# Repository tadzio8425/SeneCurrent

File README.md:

<div>
  <h1>  SeneCurrent  </h1>
</div>

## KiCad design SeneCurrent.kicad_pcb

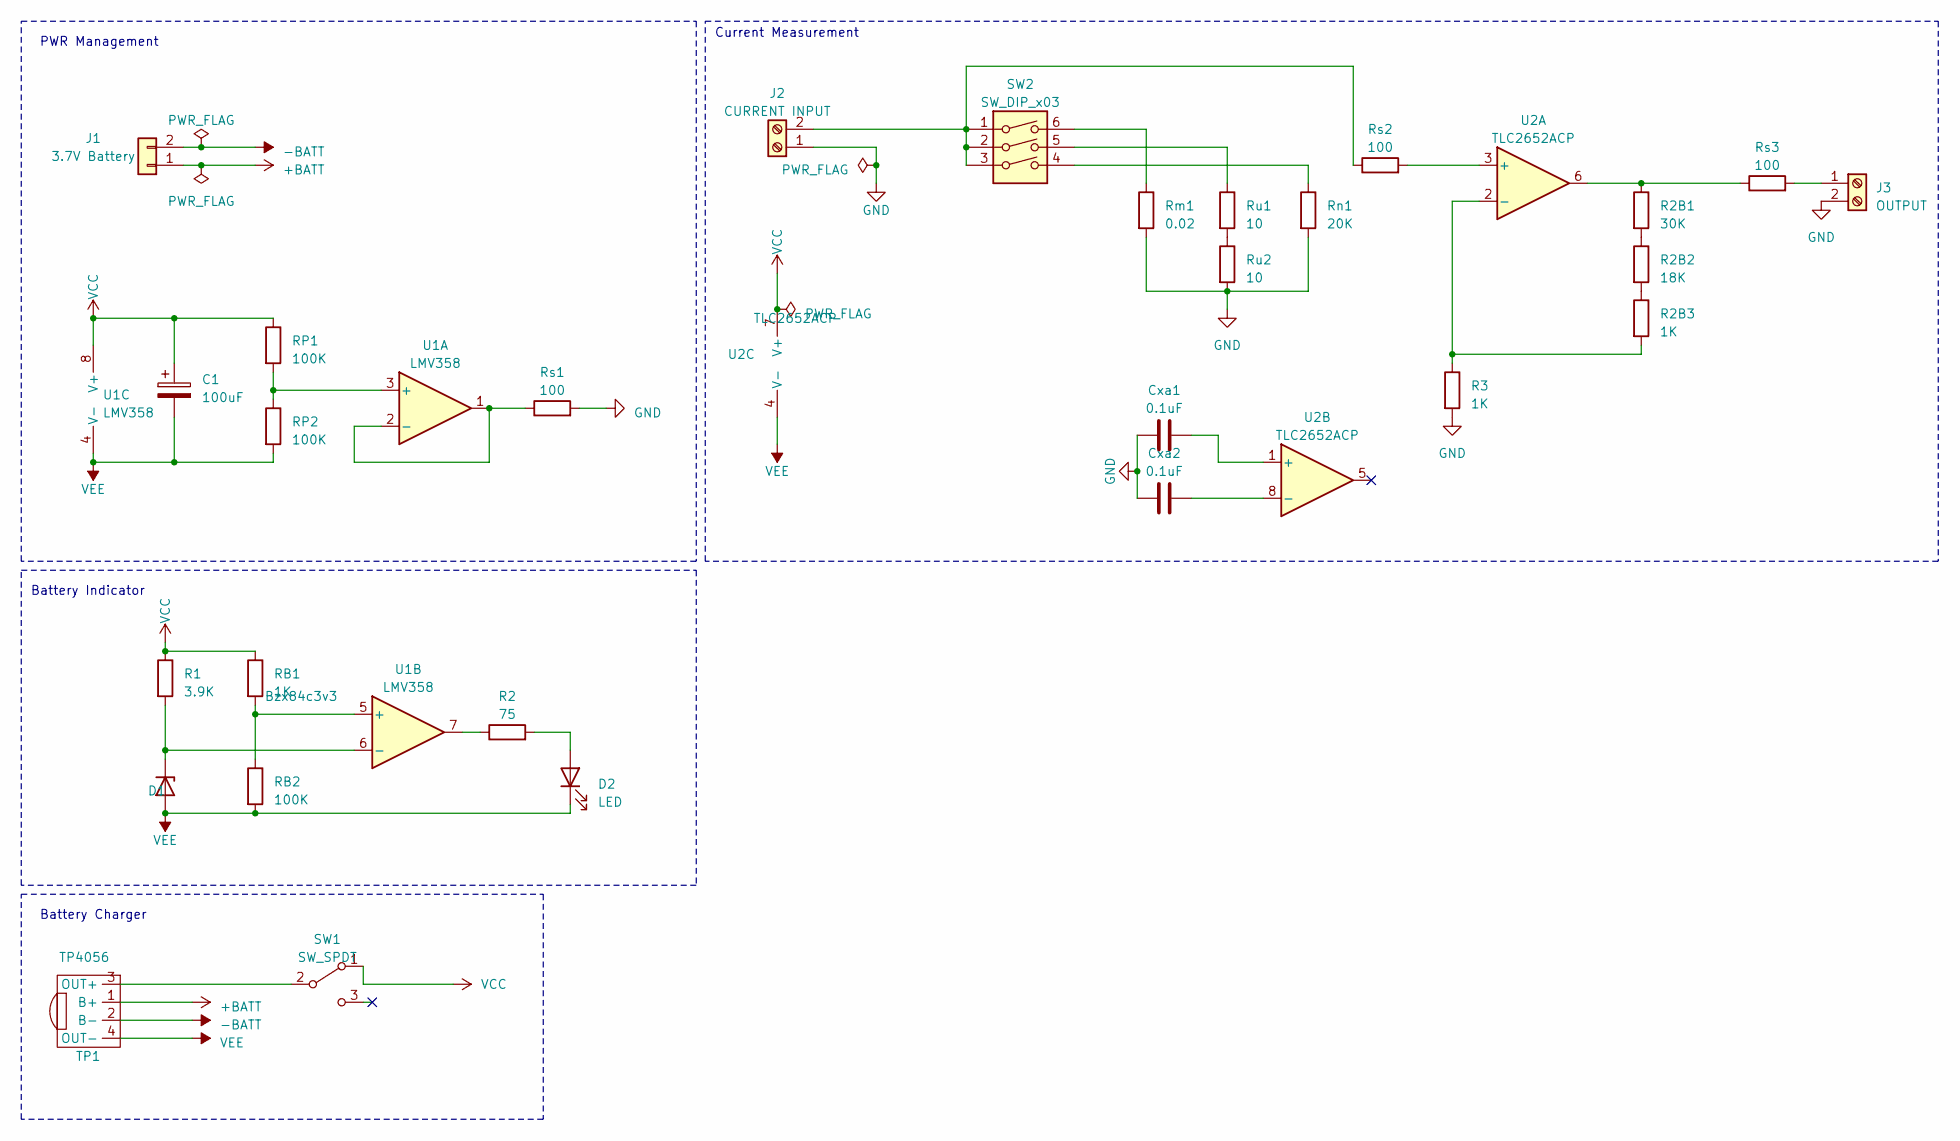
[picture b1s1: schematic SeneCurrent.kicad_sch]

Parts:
C1: 100uF; CP_Elec_5x5.9
Cxa1, Cxa2: 0.1uF; C_0805_2012Metric_Pad1.18x1.45mm_HandSolder
D1: Bzx84c3v3; D_1206_3216Metric_Pad1.42x1.75mm_HandSolder
D2: LED; LED_1206_3216Metric_Pad1.42x1.75mm_HandSolder
J1: 3.7V Battery; BatteryHolder_Keystone_1042_1x18650
J2: CURRENT INPUT; Banana_Jack_2Pin
J3: OUTPUT; Banana_Jack_2Pin
R1: 3.9K; R_1206_3216Metric_Pad1.30x1.75mm_HandSolder
R2: 75; R_1206_3216Metric_Pad1.30x1.75mm_HandSolder
R2B1: 30K; R_1206_3216Metric_Pad1.30x1.75mm_HandSolder
R2B2: 18K; R_1206_3216Metric_Pad1.30x1.75mm_HandSolder
R2B3, R3: 1K; R_1206_3216Metric_Pad1.30x1.75mm_HandSolder
RB1: 1K; R_1206_3216Metric_Pad1.30x1.75mm_HandSolder
RB2: 100K; R_1206_3216Metric_Pad1.30x1.75mm_HandSolder
RP1, RP2: 100K; R_1206_3216Metric_Pad1.30x1.75mm_HandSolder
Rm1: 0.02; ShuntRes
Rn1: 20K; R_1206_3216Metric_Pad1.30x1.75mm_HandSolder
Rs1, Rs2, Rs3: 100; R_1206_3216Metric_Pad1.30x1.75mm_HandSolder
Ru1, Ru2: 10; R_1206_3216Metric_Pad1.30x1.75mm_HandSolder
SW1: SW_SPDT; Slide_Switch_SPDT_ThroughHole
SW2: SW_DIP_x03; SW_DIP_SPSTx03_Slide_9.78x9.8mm_W7.62mm_P2.54mm
TP1: TP4056; TP4056-Module
U1: LMV358
U2: TLC2652ACP; DIP-8_W7.62mm_Socket

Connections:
+BATT: J1.1, TP1.1 (B+)
-BATT: J1.2, TP1.2 (B-)
GND: Cxa1.2, Cxa2.2, J2.1, J3.2, R3.2, Rm1.2, Rn1.2, Rs1.2, Ru2.2
unnamed: D1.2 (K), R1.2, U1.6 (-)
unnamed: D2.2 (A), R2.2
unnamed: J2.2, Rs2.1, SW2.1, SW2.2, SW2.3
unnamed: J3.1, Rs3.2
unnamed: R2.1, U1.7
unnamed: R2B1.1, Rs3.1, U2.6
unnamed: R2B1.2, R2B2.1
unnamed: R2B2.2, R2B3.1
unnamed: Rm1.1, SW2.6
unnamed: Rn1.1, SW2.4
unnamed: Ru1.1, SW2.5
unnamed: Ru1.2, Ru2.1
unnamed: SW1.2 (B), TP1.3 (OUT+)
unnamed: RP1.2, RP2.1, U1.3 (+)
unnamed: Rs1.1, U1.1, U1.2 (-)
unnamed: RB1.2, RB2.1, U1.5 (+)
unnamed: Rs2.2, U2.3 (+)
unnamed: R2B3.2, R3.1, U2.2 (-)
unnamed: Cxa1.1, U2.1 (+)
unnamed: Cxa2.1, U2.8 (-)
VCC: C1.1, R1.1, RB1.1, RP1.1, SW1.1 (A), U1.8 (V+), U2.7 (V+)
VEE: C1.2, D1.1 (A), D2.1 (K), RB2.2, RP2.2, TP1.4 (OUT-), U1.4 (V-), U2.4 (V-)

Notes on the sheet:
PWR Management
Battery Indicator
Current Measurement
Battery Charger

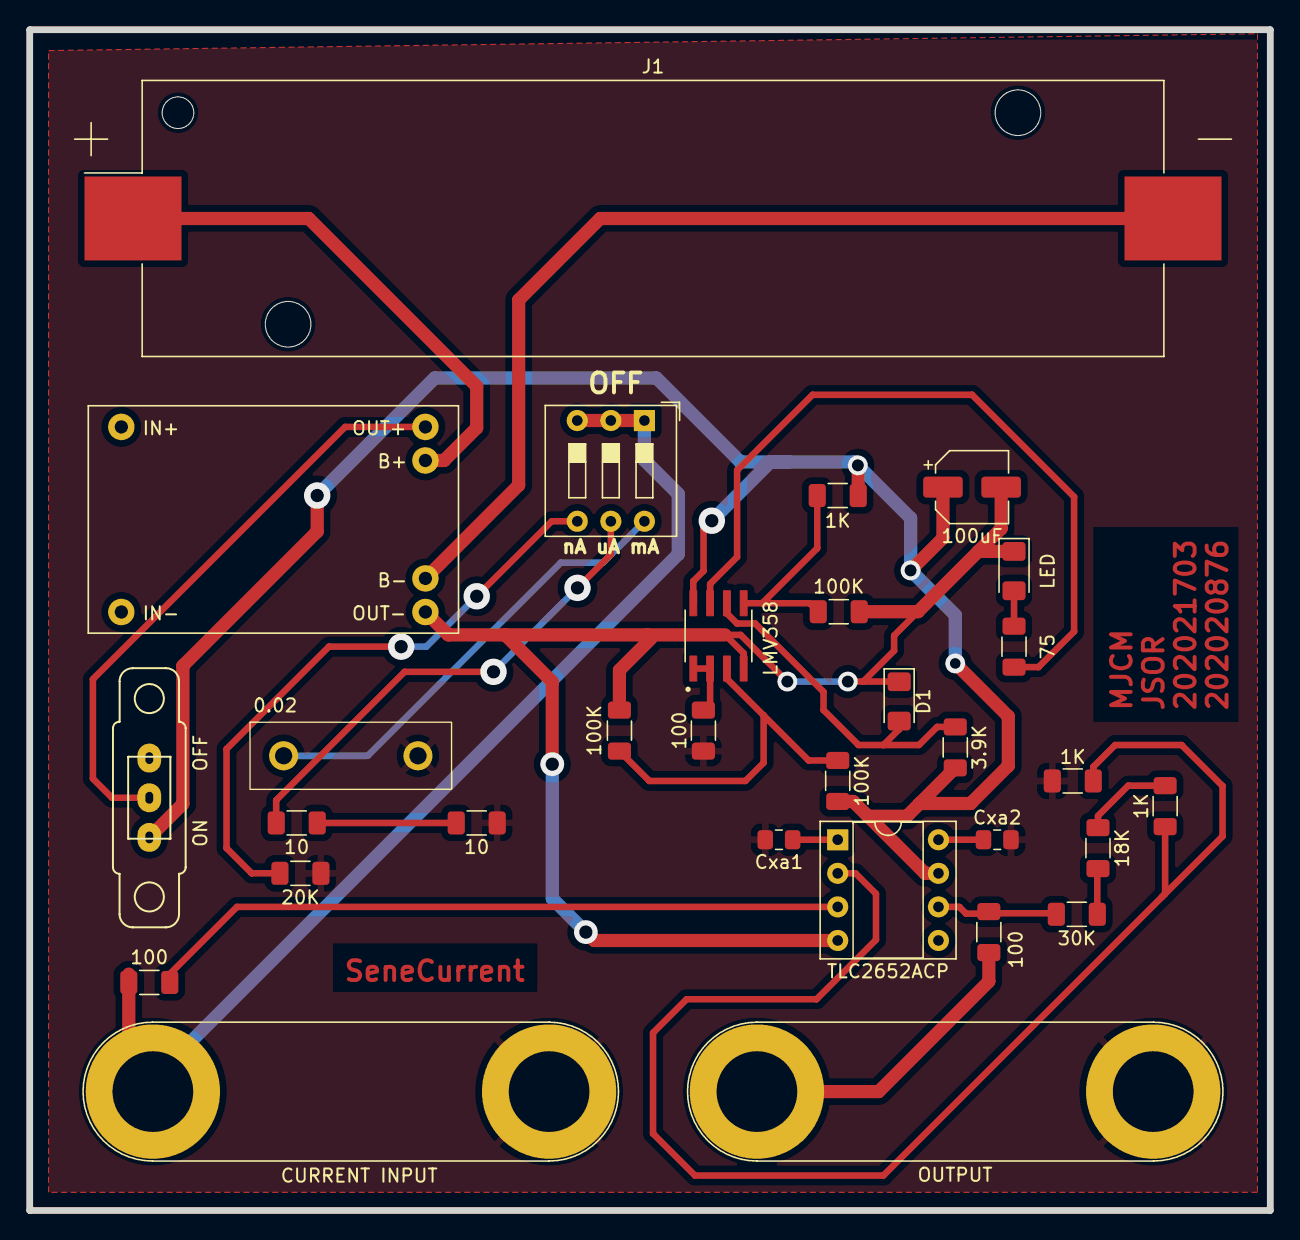
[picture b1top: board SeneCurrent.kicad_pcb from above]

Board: 2 copper layers, 93.8 x 89.3 mm, 30 parts (0 on the bottom side), 25 nets.

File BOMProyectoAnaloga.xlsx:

Id | Identificador | Huella | Cantidad | Identificación | Suministrador y ref | Precio | Comprado
1 | Rs3,Rs2,Rs1 | R_1206_3216Metric_Pad1.30x1.75mm_HandSolder | 3 | 100 | https://ja-bots.com/producto/resistencia-smd-1206-100-a-1k-o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 | 2000
2 | Rm1 | ShuntRes | 1 | 0.02 | https://ssdielect.com/magnitudes-electricas/2065-shunt-0-02o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 | 4189
3 | Ru1,Ru2 | R_1206_3216Metric_Pad1.30x1.75mm_HandSolder | 2 | 10 | https://ja-bots.com/producto/resistencia-smd-1206-de-0-a-100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 | 2000
4 | J3 | Banana_Jack_2Pin | 1 | OUTPUT | https://www.vistronica.com/conectores-cables-y-switches/cone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 | 1098
5 | J2 | Banana_Jack_2Pin | 1 | INPUT | https://www.vistronica.com/conectores-cables-y-switches/cone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 | 1098
6 | U1 | DIP-8_W7.62mm_Socket | 1 | LMV358 | https://articulo.mercadolibre.com.co/MCO-1212452687-lmv358-a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 | 9900
7 | R3 | R_1206_3216Metric_Pad1.30x1.75mm_HandSolder | 1 | 1K | https://ja-bots.com/producto/resistencia-smd-1206-de-1k-a-10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 | 2000
8 | ON | Slide_Switch_SPDT_ThroughHole | 1 | OFF | https://articulo.mercadolibre.com.co/MCO-581954587-mini-suic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 | 5000
9 | R1 | R_1206_3216Metric_Pad1.30x1.75mm_HandSolder | 1 | 3.9K | https://ja-bots.com/producto/resistencia-smd-1206-de-1k-a-10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 | 2000
10 | Cxa2,Cxa1 | C_0603_1608Metric_Pad1.08x0.95mm_HandSolder | 2 | 0.1uF | https://www.sigmaelectronica.net/producto/cc0603-0-1uf50/ | 1130
11 | C1 | CP_Elec_6.3x7.7 | 1 | 100uF | https://www.sigmaelectronica.net/producto/cond-100uf-16v/#reviews | 952
12 | SW2 | SW_DIP_SPSTx03_Slide_9.78x9.8mm_W7.62mm_P2.54mm | 1 | SW_DIP_x03 | NOVENA | 3000
13 | RB2,RP1,RP2 | R_1206_3216Metric_Pad1.30x1.75mm_HandSolder | 3 | 100K | https://ja-bots.com/producto/resistencia-smd-1206-de-100k-a-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 | 2000
14 | D2 | LED_1206_3216Metric_Pad1.42x1.75mm_HandSolder | 1 | LED | https://ja-bots.com/producto/led-smd-1206-x-10-2/ | 2000
15 | R2B1 | R_1206_3216Metric_Pad1.30x1.75mm_HandSolder | 1 | 30K | https://ja-bots.com/producto/resistencia-smd-1206-de-1k-a-10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 | 2000
16 | R2B1 | R_1206_3216Metric_Pad1.30x1.75mm_HandSolder | 1 | 18K | https://ja-bots.com/producto/resistencia-smd-1206-de-1k-a-10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 | 2000
17 | TP1 | TP4056-Module | 1 | TP4056 | https://ja-bots.com/producto/modulo-cargador-bateria-de-lipo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 | 9500
18 | J1 | BatteryHolder_Keystone_1042_1x18650 | 1 | 3.7V Battery | https://articulo.mercadolibre.com.co/MCO-657542624-bateria-r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 | 18200
19 | Rn1 | R_1206_3216Metric_Pad1.30x1.75mm_HandSolder | 2 | 20K | https://ja-bots.com/producto/resistencia-smd-1206-de-1k-a-10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 | 2000
20 | U2 | DIP-8_W7.62mm_Socket | 1 | TLC2652ACP | https://www.sigmaelectronica.net/producto/tlc2652acp/ | 15470
21 | D1 | 1206 | 1 | Zenner 3.3V | https://ssdielect.com/zener/2271-697-ll34-zmmxx.html#/549-vo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 | 700
22 | R2 | R_1206_3216Metric_Pad1.30x1.75mm_HandSolder | 1 | 75 | https://ja-bots.com/producto/resistencia-smd-1206-de-0-a-100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 | 2000
 |  |  |  |  |  | 90237

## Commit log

2023-07-30 senecurrent as fabricated
